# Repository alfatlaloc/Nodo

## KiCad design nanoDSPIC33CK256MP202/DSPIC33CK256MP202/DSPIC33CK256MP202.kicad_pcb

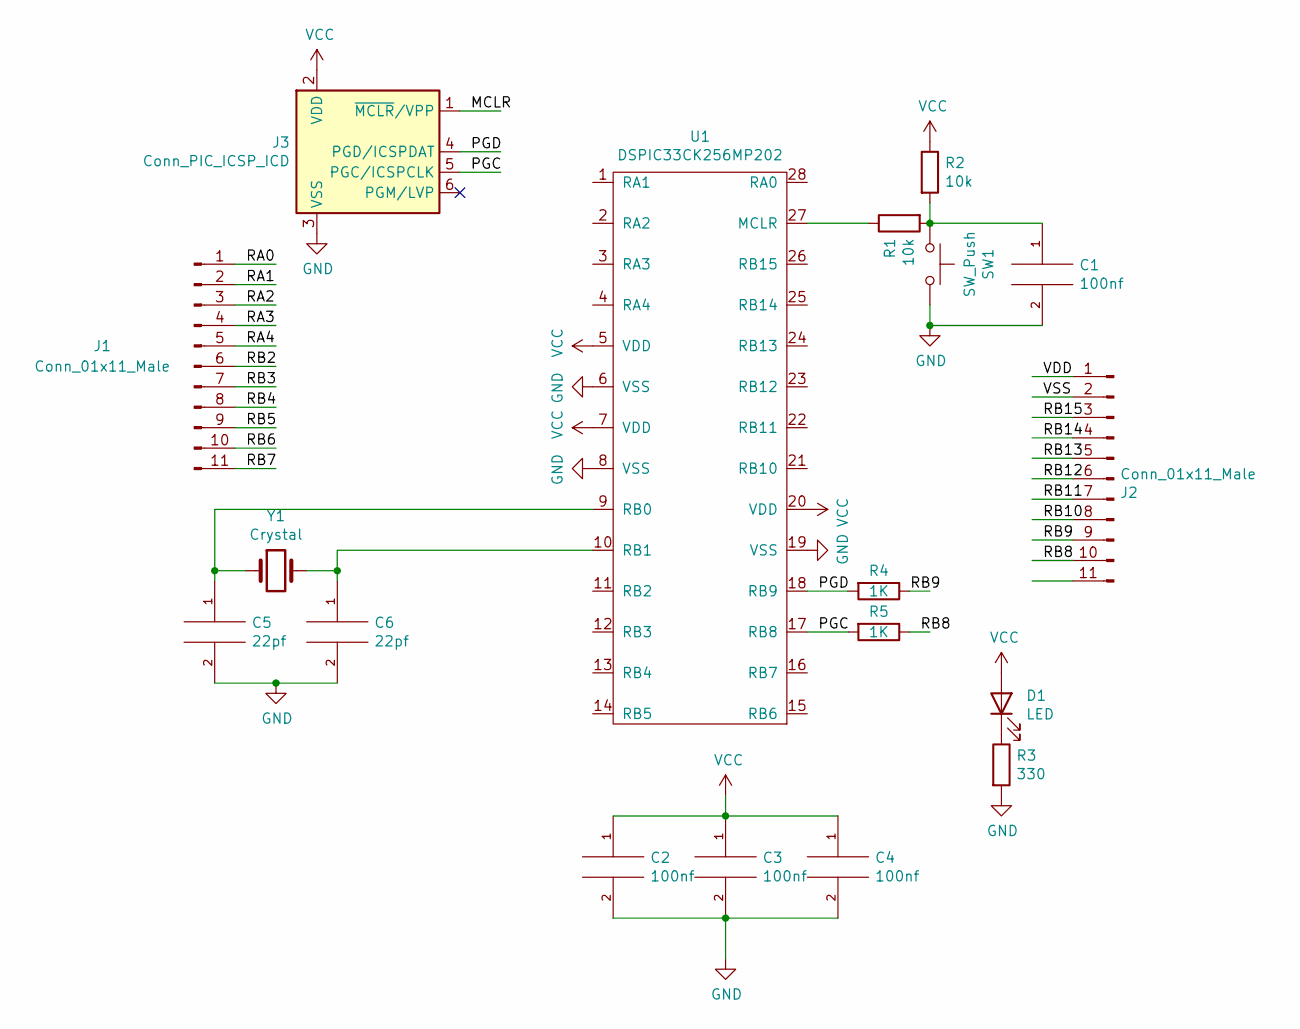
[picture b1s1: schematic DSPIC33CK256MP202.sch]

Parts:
C1, C2, C3, C4: 100nf; C_1812_4532Metric
C5, C6: 22pf; C_1812_4532Metric
D1: LED; LED_0805_2012Metric_Castellated
J1, J2: Conn_01x11_Male; PinHeader_1x11_P2.54mm_Horizontal
J3: Conn_PIC_ICSP_ICD; PinHeader_1x06_P2.54mm_Horizontal
R1, R2: 10k; R_1206_3216Metric
R3: 330; R_1206_3216Metric
R4, R5: 1K; R_1206_3216Metric
SW1: SW_Push; Panasonic_EVQPUJ_EVQPUA
U1: DSPIC33CK256MP202; DSPICBEIFI
Y1: Crystal; Crystal_SMD_Abracon_ABM3-2Pin_5.0x3.2mm

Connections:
/MCLR: J3.1 (~MCLR~/VPP)
/PGC: J3.5 (PGC/ICSPCLK), R5.2, U1.17 (RB8)
/PGD: J3.4 (PGD/ICSPDAT), R4.2, U1.18 (RB9)
/RA0: J1.1
/RA1: J1.2
/RA2: J1.3
/RA3: J1.4
/RA4: J1.5
/RB2: J1.6
/RB3: J1.7
/RB4: J1.8
/RB5: J1.9
/RB6: J1.10
/RB7: J1.11
/RB8: J2.10, R5.1
/RB9: J2.9, R4.1
/RB10: J2.8
/RB11: J2.7
/RB12: J2.6
/RB13: J2.5
/RB14: J2.4
/RB15: J2.3
/VDD: J2.1
/VSS: J2.2
GND: C1.2, C2.2, C3.2, C4.2, C5.2, C6.2, J3.3 (VSS), R3.2, SW1.2, U1.6 (VSS), U1.8 (VSS), U1.19 (VSS)
unnamed: C1.1, R1.2, R2.2, SW1.1
unnamed: C5.1, U1.9 (RB0), Y1.1
unnamed: C6.1, U1.10 (RB1), Y1.2
unnamed: D1.1 (K), R3.1
unnamed: R1.1, U1.27 (MCLR)
VCC: C2.1, C3.1, C4.1, D1.2 (A), J3.2 (VDD), R2.1, U1.5 (VDD), U1.7 (VDD), U1.20 (VDD)

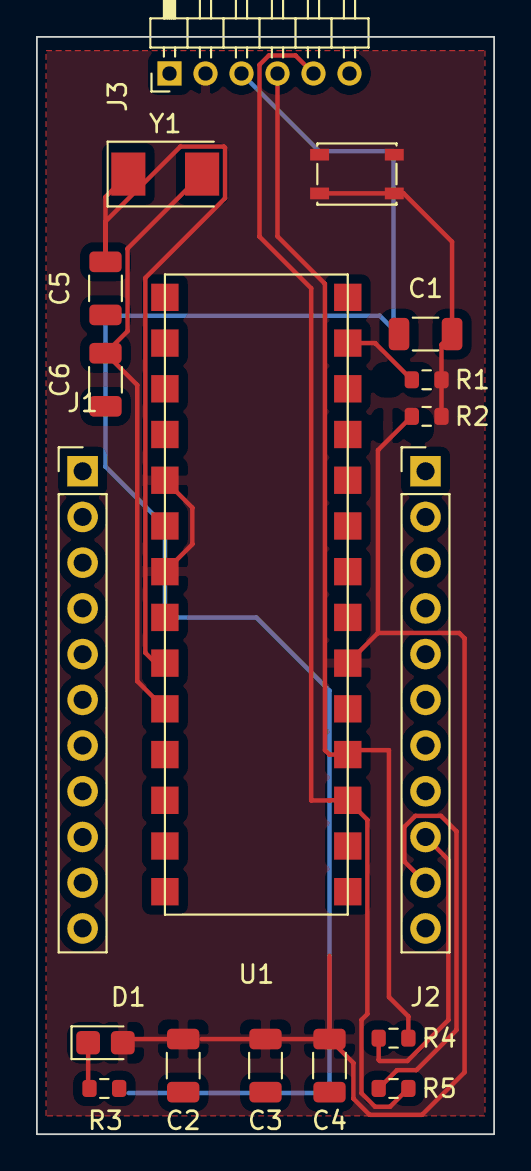
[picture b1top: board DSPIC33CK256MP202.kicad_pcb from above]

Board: 2 copper layers, 25.4 x 61.0 mm, 18 parts (0 on the bottom side), 11 nets.

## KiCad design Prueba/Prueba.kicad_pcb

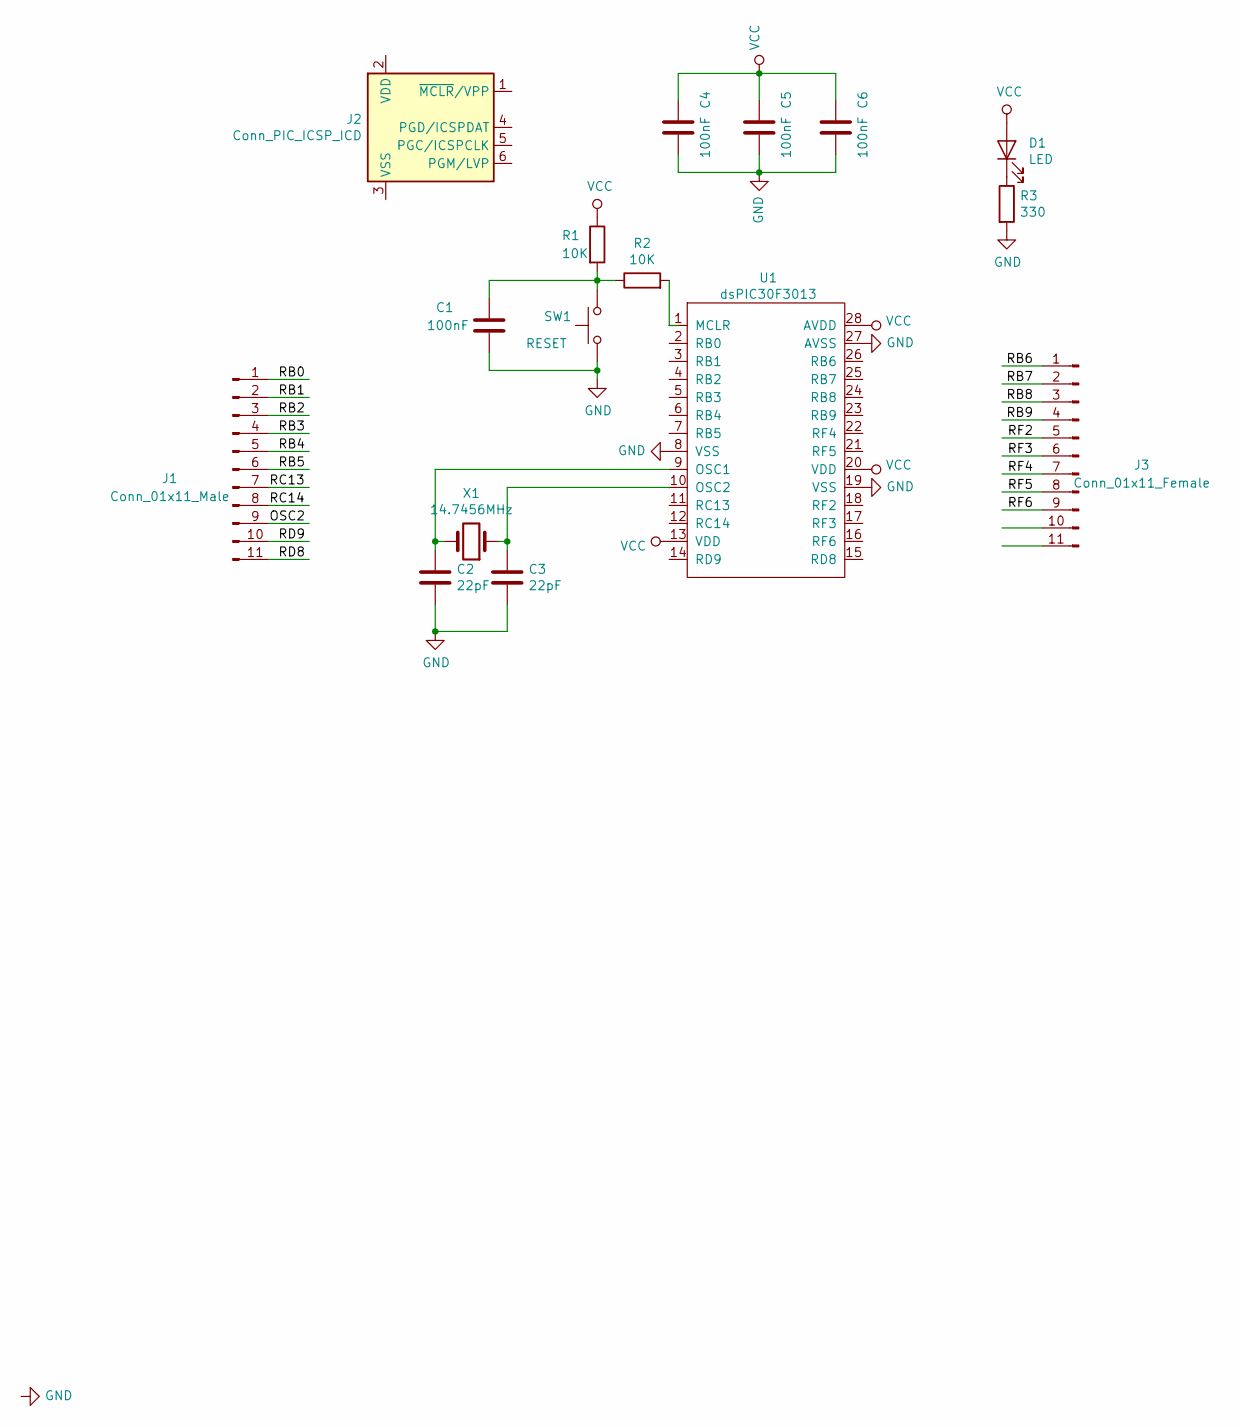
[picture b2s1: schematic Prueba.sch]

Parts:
C1, C4, C5, C6: 100nF; C_1206_3216Metric
C2, C3: 22pF; C_1206_3216Metric
D1: LED; LED_1206_3216Metric
J1: Conn_01x11_Male; PinHeader_1x11_P2.54mm_Vertical
J2: Conn_PIC_ICSP_ICD; PinHeader_1x06_P2.54mm_Horizontal
J3: Conn_01x11_Female; PinHeader_1x11_P2.54mm_Vertical
R1, R2: 10K; R_1206_3216Metric
R3: 330; R_1206_3216Metric
SW1: RESET; RESETBUTTON
U1: dsPIC30F3013; PIC30F3013
X1: 14.7456MHz; Crystal_SMD_Abracon_ABM3-2Pin_5.0x3.2mm

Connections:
/OSC2: J1.9
/RB0: J1.1
/RB1: J1.2
/RB2: J1.3
/RB3: J1.4
/RB4: J1.5
/RB5: J1.6
/RB6: J3.1
/RB7: J3.2
/RB8: J3.3
/RB9: J3.4
/RC13: J1.7
/RC14: J1.8
/RD8: J1.11
/RD9: J1.10
/RF2: J3.5
/RF3: J3.6
/RF4: J3.7
/RF5: J3.8
/RF6: J3.9
GND: C1.2, C2.2, C3.2, C4.2, C5.2, C6.2, R3.2, SW1.1, U1.8 (VSS), U1.19 (VSS), U1.27 (AVSS)
unnamed: C1.1, R1.2, R2.1, SW1.2
unnamed: C2.1, U1.9 (OSC1), X1.2
unnamed: C3.1, U1.10 (OSC2), X1.1
unnamed: D1.1 (K), R3.1
unnamed: R2.2, U1.1 (MCLR)
VCC: C4.1, C5.1, C6.1, D1.2 (A), R1.1, U1.13 (VDD), U1.20 (VDD), U1.28 (AVDD)

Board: 2 copper layers, 16 parts (0 on the bottom side), 7 nets, no tracks yet.

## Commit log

2020-05-21 DSPIC30f4013
2020-05-22 Oscilador, reset y caps
2020-05-31 ICSP
2020-08-09 Nuevo integrado
2020-08-09 Create dsPIC33CH128MP502
2020-08-10 Nodo
2020-08-12 Correcion iscp
